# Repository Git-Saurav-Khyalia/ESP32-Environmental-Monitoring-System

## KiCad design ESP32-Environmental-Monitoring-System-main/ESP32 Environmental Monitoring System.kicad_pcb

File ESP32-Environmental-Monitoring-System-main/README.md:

# ESP32-Based Environmental Monitoring System

An embedded environmental monitoring system built around the ESP32 microcontroller and DHT11 temperature and humidity sensor. The system acquires environmental data, processes sensor readings, and demonstrates an end-to-end embedded hardware development workflow, from circuit simulation and firmware development to PCB design and manufacturing file generation.

## Overview

This project explores the development of a microcontroller-based environmental monitoring system, with an emphasis on embedded programming, sensor interfacing, circuit design, and PCB development.

The ESP32 communicates with the DHT11 sensor to obtain temperature and humidity measurements. The firmware processes the readings and makes the data available for monitoring.

The hardware design was developed using KiCad, while Wokwi was used to simulate the circuit before potential physical implementation.

### Key Features

- Real-time temperature and humidity acquisition using a DHT11 sensor.
- Embedded firmware development using C/C++ and the Arduino framework.
- Sensor interfacing with the ESP32.
- Virtual circuit simulation using Wokwi.
- Schematic capture and PCB layout design using KiCad.
- PCB design-rule validation and Gerber file generation.

## System Architecture

The system consists of three primary components:

1. **ESP32 microcontroller:** Controls sensor communication and processes measurement data.
2. **DHT11 sensor:** Measures ambient temperature and relative humidity.
3. **Monitoring interface:** Displays or outputs sensor readings through the interface implemented in the firmware.

### Data Flow

`DHT11 Sensor → ESP32 → Data Processing → Serial Output / Configured Monitoring Interface`

The ESP32 reads measurements from the sensor, processes the data, and outputs the readings according to the firmware implementation.

## Hardware Components

| Component                        | Purpose                                       |
| -------------------------------- | --------------------------------------------- |
| ESP32-WROOM-32 development board | Main microcontroller platform                 |
| DHT11 sensor                     | Temperature and humidity measurement          |
| Connecting wires and connectors  | Electrical interconnections                   |
| Supporting passive components    | Circuit support, where required by the design |

Refer to the circuit schematic for the actual component connections and values.

## Tools and Technologies

| Tool / Technology | Application                              |
| ----------------- | ---------------------------------------- |
| ESP32             | Embedded processing                      |
| Embedded C/C++    | Firmware development                     |
| Arduino IDE       | Firmware development and compilation     |
| Wokwi             | Circuit and firmware simulation          |
| KiCad             | Schematic capture and PCB layout         |
| Gerber files      | PCB fabrication preparation              |
| Git and GitHub    | Source control and project documentation |

## Repository Structure

```text
ESP32-Environmental-Monitoring-System/
│
├── Arduino Code/
│   └── ESP32 Environmental Monitoring System.ino
│
├── Gerber/
│   └── PCB manufacturing output files
│
├── ESP32 Environmental Monitoring System.kicad_pro
├── ESP32 Environmental Monitoring System.kicad_sch
├── ESP32 Environmental Monitoring System.kicad_pcb
│
└── README.md
```

*The directory structure above describes the expected repository organization. File names and folders may differ in the actual repository.*

## Circuit Simulation

The circuit can be explored through the Wokwi online simulator.

**[Open the Wokwi Simulation](https://wokwi.com/projects/472157564927177729)**

The simulation can be used to examine the circuit configuration and observe firmware behavior without requiring physical electronic components.

Simulation results demonstrate the behavior supported by the virtual environment; they do not independently verify the performance of a fabricated circuit.

## PCB Design Workflow

The PCB design workflow uses KiCad to translate the circuit concept into a board layout.

The main stages include:

1. Creating the circuit schematic.
2. Assigning appropriate component footprints.
3. Transferring components and connections to the PCB editor.
4. Arranging components and routing signal and power connections.
5. Running electrical rule checks (ERC) and design rule checks (DRC).
6. Generating Gerber and drill files for potential manufacturing.

Gerber files represent manufacturing outputs and do not, by themselves, establish that the board has been fabricated or physically validated.

## Firmware Workflow

The firmware is developed using C/C++ with the Arduino framework.

The expected firmware workflow includes:

1. Initializing the ESP32 and sensor interface.
2. Reading temperature and humidity measurements from the DHT11.
3. Handling sensor initialization or measurement failures, where implemented.
4. Processing and formatting the readings.
5. Outputting the measurements through the configured monitoring interface.

Refer to the Arduino source file for the implementation details and the interfaces actually supported by the firmware.

## Validation and Testing

The project can be evaluated through simulation, firmware compilation, and PCB design checks.

| Validation activity   | Purpose                                          |
| --------------------- | ------------------------------------------------ |
| Firmware compilation  | Identify build errors                            |
| Wokwi simulation      | Examine simulated circuit and firmware behavior  |
| Sensor-reading checks | Verify expected behavior within the simulation   |
| KiCad ERC             | Identify electrical schematic issues             |
| KiCad DRC             | Check PCB layout against configured design rules |
| Gerber inspection     | Review manufacturing output files                |

Physical measurements, soldering validation, and hardware bring-up require a fabricated and assembled board. These should be documented separately if performed.

## Project Scope and Limitations

This project focuses on the fundamentals of embedded electronics development, including microcontroller programming, sensor interfacing, circuit simulation, and PCB design.

The current design uses a DHT11 sensor and is intended as a foundational environmental monitoring application. Wireless communication, battery-powered operation, and advanced power optimization are possible future extensions rather than assumed features.

## Future Improvements

- Add wireless data transmission using ESP32 Wi-Fi or Bluetooth Low Energy.
- Introduce configurable sensor sampling intervals.
- Evaluate low-power operating modes.
- Add a graphical dashboard for environmental measurements.
- Extend sensor error handling and data validation.
- Fabricate and assemble the PCB for physical testing.
- Measure power consumption and validate system performance on hardware.

## License

Refer to the repository's license file for the applicable terms governing use, modification, and redistribution.

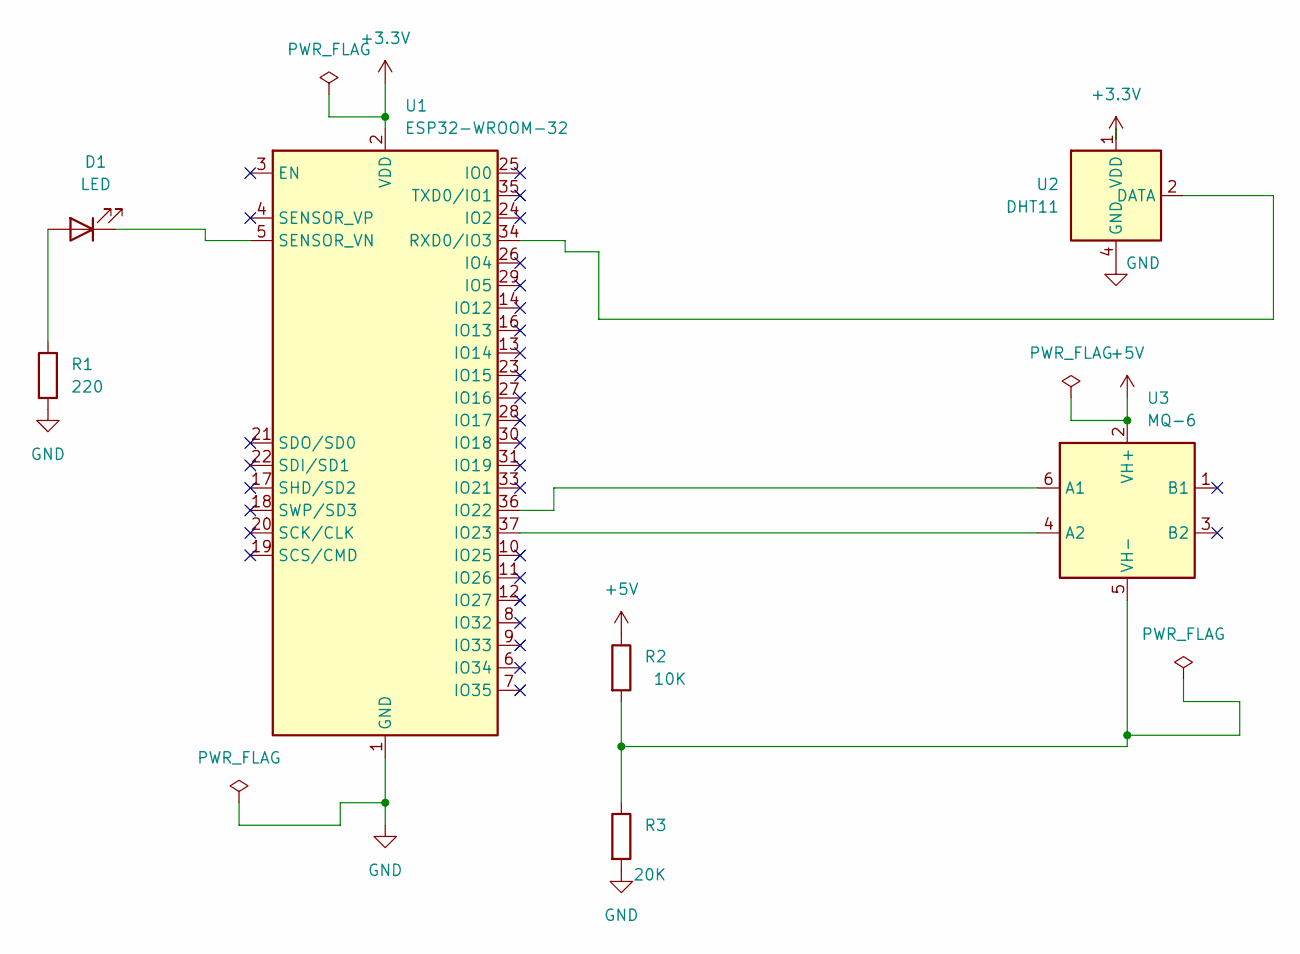
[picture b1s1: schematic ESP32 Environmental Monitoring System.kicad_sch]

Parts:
D1: LED; LED_D5.0mm
R1: 220; R_Axial_DIN0207_L6.3mm_D2.5mm_P10.16mm_Horizontal
R2: 10K; R_Axial_DIN0207_L6.3mm_D2.5mm_P10.16mm_Horizontal
R3: 20K; R_Axial_DIN0207_L6.3mm_D2.5mm_P10.16mm_Horizontal
U1: ESP32-WROOM-32
U2: DHT11; Aosong_DHT11_5.5x12.0_P2.54mm
U3: MQ-6

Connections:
+3.3V: U1.2 (VDD), U2.1 (VDD)
+5V: R2.1, U3.2 (VH+)
GND: R1.2, R3.2, U1.1 (GND), U1.15 (GND), U1.38 (GND), U1.39 (GND), U2.4 (GND)
unnamed: D1.2 (A), R1.1
unnamed: D1.1 (K), U1.5 (SENSOR_VN)
unnamed: U1.36 (IO22), U3.6 (A1)
unnamed: U1.37 (IO23), U3.4 (A2)
unnamed: U1.34 (RXD0/IO3), U2.2 (DATA)
unnamed: R2.2, R3.1, U3.5 (VH-)

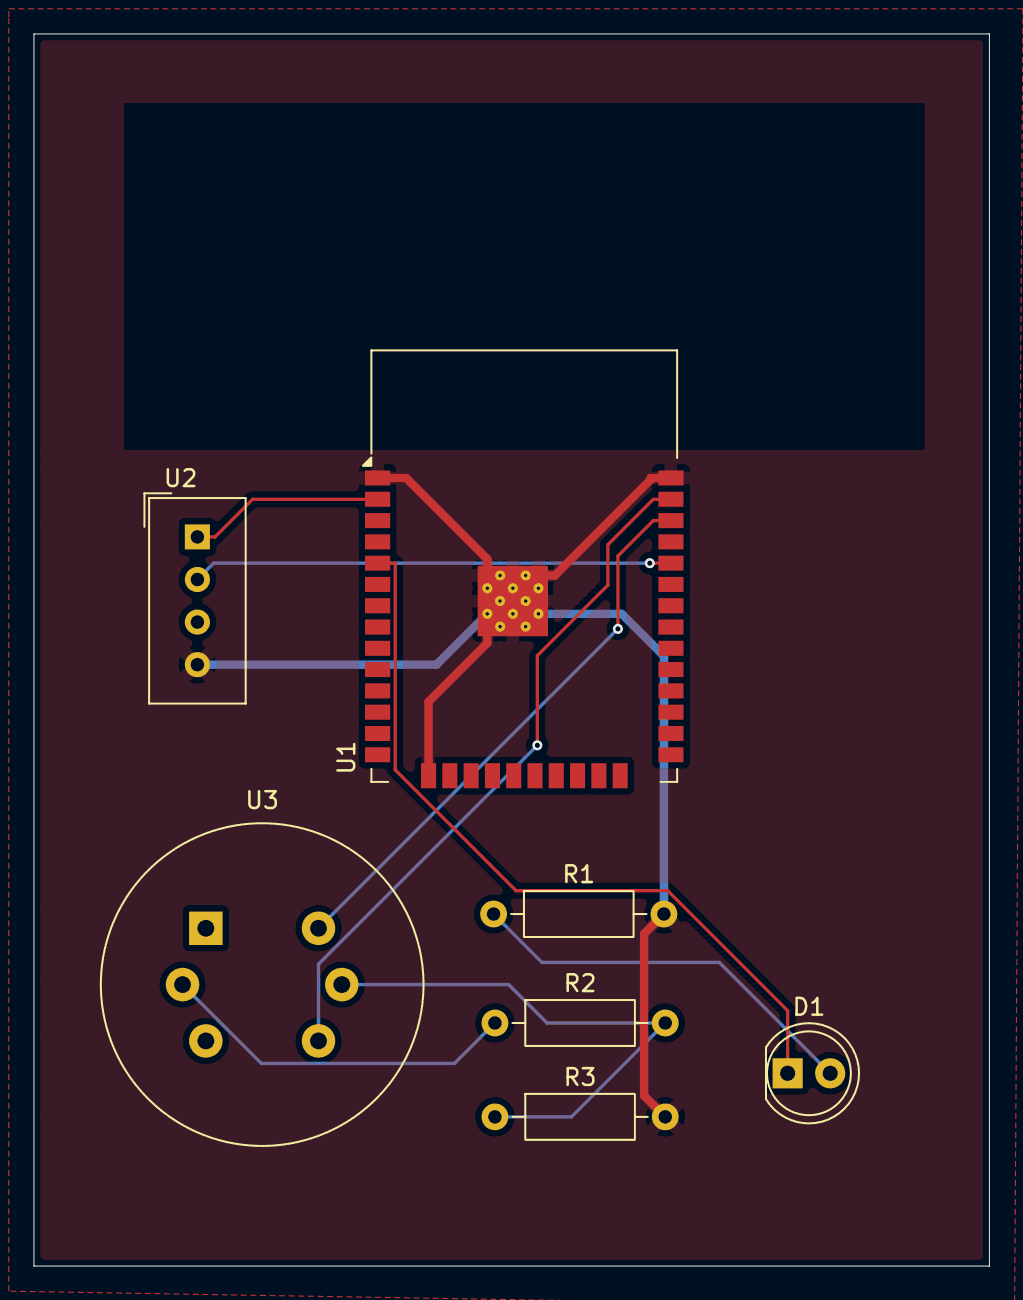
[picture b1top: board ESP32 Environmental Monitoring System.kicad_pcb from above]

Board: 2 copper layers, 57.0 x 73.5 mm, 7 parts (0 on the bottom side), 9 nets.
